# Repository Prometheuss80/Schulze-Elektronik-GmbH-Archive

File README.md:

# Schulze Elektronik GmbH Archive and Reverse Engineering Project

An independent preservation, documentation and reverse engineering project dedicated to older battery chargers, balancers and related equipment from **Schulze Elektronik GmbH**.

The purpose of this repository is to preserve technical knowledge about these devices and to make the results of ongoing reverse engineering available to the public.

Many Schulze devices are still in use today, but detailed technical information, service documentation and development tools are increasingly difficult to find.

This project attempts to document the operation of these devices and provide information and tools that can help other enthusiasts with their repair, maintenance, study and further development.

---

## Projects

### Schulze ISL8-936G

Reverse engineering of the Schulze **ISL8-936G** charger family.

Current research areas include:

* Siemens 80C537 Processor Architecture
* ROM Firmware Analysis
* External SRAM and Timekeeper M48T08
* 93LC46 EEPROM
* Firmware Execution Tracing
* Address Bus Capture and Logging
* Firmware Reconstruction
* LCD Control and Display Routines
* Keyboard and I/O Decoding
* Serial Communication
* Command Tables and Internal Firmware Structures
* Measurement System
* Factory Calibration Routines
* Service and Diagnostic Functions
* Hardware Documentation
* Development of Custom Reverse Engineering Tools

The main part of this project is the development of a complete hardware/software system capable of monitoring firmware execution and reconstructing the internal operation of the charger.

---

### Schulze ISL6-636+

Reverse Engineering and Documentation of the Schulze ISL6-636+ Charger

The research includes:

* Siemens 80C535 processor
* ROM firmware
* 93LC46 EEPROM
* HD44780 compatible LCD
* keyboard interface
* serial communication
* firmware routines
* measurement and calibration functions
* hardware documentation

ISL6 provides an interesting comparison with the later and considerably more complex ISL8 architecture.

---

### XCAL for ISL8

Research and documentation on the Schulze calibration device and automatic calibration procedures.

This research was successfully confirmed and completed. XCAL has the same function as the original Schulze device.

It is a HW switch of specified voltages for charger calibration. This BETA test module was assembled, programmed and successfully tested.

The goal was to understand the original calibration system and reproduce the functionality needed to calibrate the existing Schulze device.

---

### XTOOLS for ISL8

Research and documentation on the Schulze calibration device and automatic calibration procedures.

This XTOOLS module was the first functional SW tool for reading and writing calibrations stored in the M48T08 timekeeper in the ISL8-936G. The first research lasted three years and revealed the way to use calibration constants.

It was manufactured and successfully tested, operating on the principle of a ROM adapter, with an IO switch ROM with XTOOLS and a ROM with FW850EN.

The goal was to understand the original calibration system and reproduce the functionality needed to calibrate the existing Schulze device.

The original standalone XTOOLS remains part of the archive. A later, integrated XTOOLS implementation has also been developed for the ISL8 firmware, including calibration editing and Timekeeper service functions.

---

### ISL6 XTOOLS and GUI

Completed XTOOLS and GUI development projects for the ISL6 family will be documented separately in this archive. Their project pages will describe supported models, implementation details and hardware testing.

---

### LipoProfiBal06

Hardware analysis of the Schulze LipoProfiBal08 and LipoProfiBal14 battery balancer.

This project includes:

* reverse engineering of the original hardware
* measurement system analysis
* power stage balancing
* MOSFET control
* isolated gate control circuits
* current measurement
* power supply architecture
* communication interface
* development of a modern replacement printed circuit board (PCB)

The new printed circuit board is to maintain the principles of operation of the original device while using components that are available today.

---

## Factory Calibration Research

Some Schulze charger firmware contains factory calibration and diagnostic functions that are typically inaccessible to the user.

Part of this project is to investigate these routines and document their operation. A number of ISL8 chargers have been successfully exposed and run as factory calibration.

Where firmware modifications are required, the preferred approach of this repository is to provide **patches and patching tools, rather than redistributing complete copyrighted firmware images**.

The user should obtain the original firmware from their own device and apply the documented modification locally.

A hardware-tested **Factory Calibration F2 Patcher** is available for ISL8 firmware versions **8.10 DE, 8.10 EN, 8.50 DE and 8.50 EN**. It enables access to the existing factory calibration procedure through F2, changes the displayed firmware identification, and updates the modification date and time. The patching tool verifies the SHA-256 of the user-supplied original firmware and does not redistribute Schulze firmware images.

---

## Author

**Martin Stránský (Prometheuss80)**

Independent research, firmware reverse engineering, development, hardware analysis and testing.

Copyright © 2026 Martin Stránský (Prometheuss80).

GitHub: [Prometheuss80](https://github.com/Prometheuss80)

---

## Licensing

Original tools and code authored for this archive may be released under the **MIT License**; see the `LICENSE` file or the license stated within each project directory for the exact scope.

The MIT License does **not** apply to original Schulze Elektronik firmware or third-party materials unless their respective rights holders authorize it. Individual project directories may have their own licensing terms.

---

## Repository Philosophy

This repository is primarily intended as a **technical archive and resource for collaborative research**.

The project is being developed in my spare time and it is not possible for me to work on all areas at the same time.

Anyone interested in a specific part of the project is welcome to study the available materials, create a fork and continue the research independently.

Useful discoveries, fixes, documentation and improvements are welcome.

It is not necessary to understand the entire system. Individual areas such as firmware analysis, 8051 assembly, analog electronics, PCB design, calibration, communication protocols or software tools can be explored independently.

---

## Contributions

Contributions are welcome.

You can:

* fork the repository
* explore any piece of hardware or firmware
* improve the documentation
* develop analytical tools
* verify existing knowledge
* submit fixes
* open an Issue with additional information
* submit a Pull Request with improvements

Since this is a project focused on preservation and leisure research, responses to Issues and Pull Requests may not always be immediate.

---

## Original material from Schulze

This repository distinguishes between:

1. original work created within the scope of this reverse engineering project and

2. copyrighted material originally created by Schulze Elektronik GmbH.

Reverse engineering notes, original software tools, measurements, photos, diagrams, and newly created documentation may be published here.

Original firmware images, manuals, and other copyrighted material from Schulze will only be included where it is known that redistribution rights allow it.

If redistribution rights are not clear, the repository will instead document the material and provide information needed for users who already own the original files or hardware.

---

## Security

Battery chargers and balancers can operate with significant electrical power.

Modified firmware, calibration procedures, and experimental hardware can disable or bypass normal protection mechanisms.

Improper calibration or modification can lead to inaccurate voltage or current measurements, battery damage, equipment damage, fire, or other hazardous conditions.

The information in this repository is provided for research, repair, and educational purposes. Anyone reproducing experiments or modifications is responsible for verifying the results and using appropriate safety precautions.

---

## Project Status

**Work in progress.**

A significant amount of reverse engineering has already been completed, particularly for the ISL8 platform. The standalone ISL8 XTOOLS, integrated ISL8 XTOOLS, ISL6 XTOOLS and ISL6 GUI projects have reached working, hardware-tested milestones. Other investigations and documentation remain ongoing.

This independent archive is maintained by Martin Stránský (Prometheuss80).

It is not affiliated with, sponsored by, or endorsed by Schulze Elektronik.

All trademarks and original product names remain the property of their respective owners.

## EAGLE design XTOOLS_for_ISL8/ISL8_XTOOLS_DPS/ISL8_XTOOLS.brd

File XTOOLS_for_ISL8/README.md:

# XTOOLS for Schulze ISL8

**XTOOLS** is an independent service and maintenance tool developed for the **Schulze ISL8 battery charger**.

It was the first project created during the ISL8 reverse-engineering work and originally started as a tool for accessing and managing the charger voltage calibration data.

Unlike a PC-based diagnostic utility, **XTOOLS runs directly on the original ISL8 hardware**.

It contains its own initialization routines and does not require the original Schulze firmware to operate.

---

## Overview

After startup, XTOOLS performs the initialization required to take control of the ISL8 hardware.

This includes:

* initialization of the main CPU
* initialization and configuration of the LCD
* initialization of required peripherals
* configuration of the charger hardware
* placing the charger power circuitry into a safe idle state
* initialization of the memory interfaces

After the hardware initialization is complete, the XTOOLS service environment is started.

The program then provides direct access to selected service and maintenance functions of the charger.

---

## Calibration Data

XTOOLS was originally developed to investigate and service the ISL8 voltage calibration system.

The tool can:

* read the existing calibration values
* display calibration information
* access calibration data stored in the Timekeeper memory
* write calibration values back to the Timekeeper

This made it possible to investigate the calibration system independently of the original charger firmware.

---

## Timekeeper Service

The ISL8 uses a Timekeeper memory for persistent configuration and operating data.

XTOOLS provides service functions for this memory, including:

* reading stored data
* writing selected data
* clearing the Timekeeper contents
* preparing a replacement Timekeeper for installation

This is particularly useful when the original Timekeeper has failed or must be replaced.

### New Timekeeper Initialization

XTOOLS provides a procedure for correctly preparing a new Timekeeper for use in an ISL8 charger.

During this process, the tool restores information required by the charger and reconstructs the charger serial number using data stored separately in an EEPROM on the ISL8 main board.

This makes XTOOLS an important service tool when replacing a failed Timekeeper device.

---

## User Data Service

XTOOLS also provides maintenance functions for selected user configuration data.

Available functions include:

* user password reset
* user name reset
* clearing selected persistent user data

These functions can be useful when servicing a charger for which the original user configuration is no longer known.

---

## Standalone Operation

One of the important characteristics of XTOOLS is that it is a **standalone firmware environment**.

The original Schulze ISL8 firmware is not required for XTOOLS operation.

XTOOLS performs its own:

1. CPU initialization
2. LCD initialization
3. hardware initialization
4. safe-state configuration
5. memory initialization
6. service application startup

The ISL8 therefore effectively operates as dedicated XTOOLS service hardware while the tool is active.

---

## XTOOLS Hardware Adapter

The project includes a dedicated hardware adapter that allows the ISL8 to switch between the original charger ROM and the XTOOLS ROM.

The adapter makes it possible to retain normal operation of the charger while providing access to the independent XTOOLS service environment when required.

The switching system is controlled by a **PIC microcontroller**.

---

## Repository Contents

This directory contains the complete XTOOLS project, including:

### XTOOLS Firmware

The complete source project for the XTOOLS firmware.

The firmware was developed using the **Keil development environment**.

### XTOOLS Adapter

Complete hardware project for the XTOOLS adapter used with the ISL8 charger.

### PCB Manufacturing Data

Manufacturing files for the XTOOLS adapter PCB, including Gerber data required for PCB production.

### PIC Switch Controller

Source/project files for the PIC microcontroller responsible for switching between:

* the original ISL8 ROM
* the XTOOLS ROM

This allows the charger to operate normally with its original firmware or boot into XTOOLS for servicing.

---

## Project Purpose

XTOOLS was created primarily as a **repair, calibration, preservation and reverse-engineering tool** for existing Schulze ISL8 chargers.

The project demonstrates that the ISL8 hardware can be initialized and operated independently of the original firmware and provides direct access to service functions that are useful when maintaining aging hardware.

In particular, XTOOLS can assist with:

* calibration data investigation
* calibration data backup and restoration
* Timekeeper replacement
* Timekeeper initialization
* recovery of charger identification data
* password recovery/reset
* user configuration reset
* hardware research and reverse engineering

---

## Important: Back Up Original Data

Before modifying or clearing the Timekeeper, always create a backup of the original contents whenever possible.

Some data stored in the charger may be unique to the individual device.

Do not erase or overwrite the original memory until a verified backup has been created.

---

## Safety Warning

XTOOLS operates directly on the hardware of a battery charger.

While XTOOLS initializes the charger hardware into an idle state before entering the service application, modifications to calibration data or persistent memory can affect subsequent charger operation.

Incorrect calibration data can cause incorrect voltage measurement and may result in unsafe battery charging.

After modifying calibration or replacing persistent memory, the charger should be fully verified and calibrated before being returned to normal operation.

Use this project only if you understand the hardware and the consequences of modifying its persistent configuration.

---

## Development Status

XTOOLS is a functional project developed from reverse engineering of the Schulze ISL8 hardware.

Additional documentation will be added as the historical development files, hardware documentation and source code are organized for public release.

---

## Disclaimer

XTOOLS is an independent project.

It is not an official Schulze Elektronik product and is not affiliated with, sponsored by, or endorsed by Schulze Elektronik.

Schulze product names are used only to identify the hardware for which this service tool was developed.

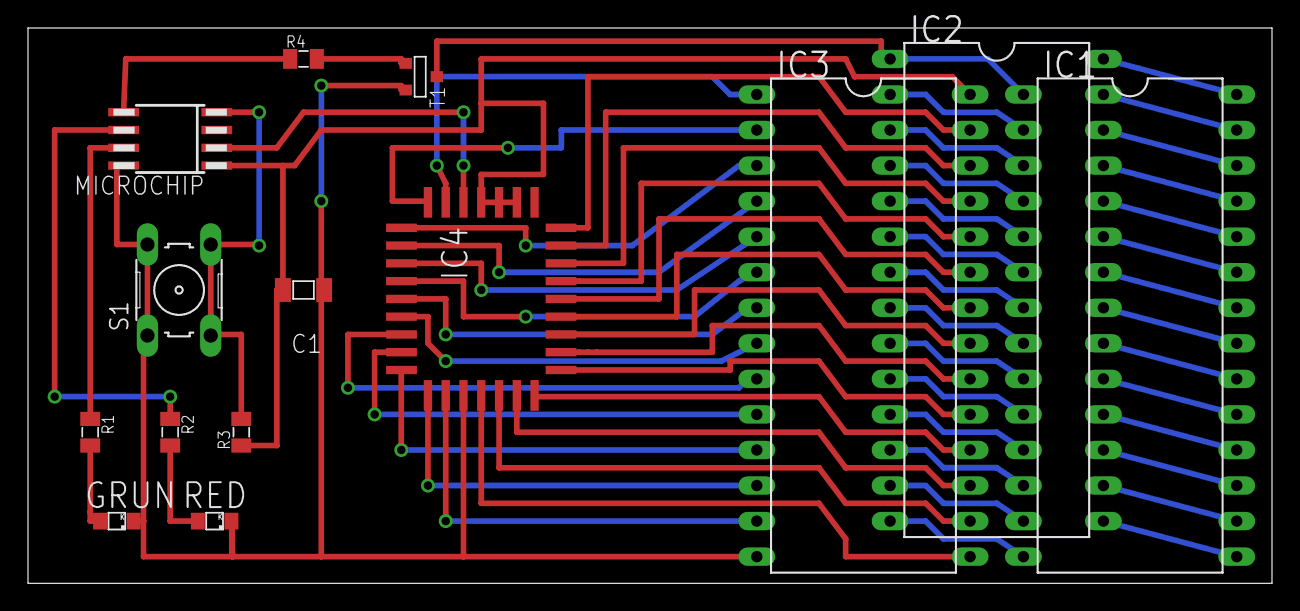
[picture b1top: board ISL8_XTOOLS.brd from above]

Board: 2 copper layers, 88.9 x 39.7 mm, 14 parts (0 on the bottom side), 64 nets.

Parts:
C1: 100nF; 1206
GRUN: ISL_8; HSMC670
IC1: DIP28_ISL8_TMKPR; DIL28-6
IC2: DIP28_XTOOLS_TMKPR; DIL28-6
IC3: DIP28_ISL8_EPROM; DIL28-6
IC4: W27C010; PLCC32R
MICROCHIP: PIC12C509SM; SO-08M
R1, R2, R4: 1k; 0805
R3: 10k; 0805
RED: XTOOLS; HSMC670
S1: SWITCH; B3F-10XX
T1: RESET; SOT-23

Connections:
0V: C1.1, GRUN.K, IC3.14, IC4.16, MICROCHIP.8, RED.K, S1.1, S1.2, T1.2
+5V: C1.2, IC3.28, IC4.1, IC4.31, IC4.32, MICROCHIP.1, R3.1
A0: IC3.10, IC4.12
A1: IC3.9, IC4.11
A2: IC3.8, IC4.10
A3: IC3.7, IC4.9
A4: IC3.6, IC4.8
A5: IC3.5, IC4.7
A6: IC3.4, IC4.6
A7: IC3.3, IC4.5
A8: IC3.25, IC4.27
A9: IC3.24, IC4.26
A10: IC3.21, IC4.23
A11: IC3.23, IC4.25
A12: IC3.2, IC4.4
A13: IC3.26, IC4.28
A14: IC3.27, IC4.29
A15: IC3.1, IC4.3
A16: IC4.2, MICROCHIP.2
CE: IC3.20, IC4.22
D0: IC3.11, IC4.13
D1: IC3.12, IC4.14
D2: IC3.13, IC4.15
D3: IC3.15, IC4.17
D4: IC3.16, IC4.18
D5: IC3.17, IC4.19
D6: IC3.18, IC4.20
D7: IC3.19, IC4.21
unnamed: IC1.1, IC2.1, T1.3
unnamed: MICROCHIP.7, R1.1
unnamed: MICROCHIP.6, R2.1
unnamed: R2.2, RED.A
unnamed: GRUN.A, R1.2
unnamed: MICROCHIP.5, R4.1
unnamed: MICROCHIP.4, R3.2, S1.3, S1.4
unnamed: IC1.2, IC2.2
unnamed: IC1.3, IC2.3
unnamed: IC1.4, IC2.4
unnamed: IC1.5, IC2.5
unnamed: R4.2, T1.1
unnamed: IC1.6, IC2.6
unnamed: IC1.7, IC2.7
unnamed: IC1.8, IC2.8
unnamed: IC1.9, IC2.9
unnamed: IC1.10, IC2.10
unnamed: IC1.11, IC2.11
unnamed: IC1.12, IC2.12
unnamed: IC1.13, IC2.13
unnamed: IC1.14, IC2.14
unnamed: IC1.15, IC2.15
unnamed: IC1.16, IC2.16
unnamed: IC1.17, IC2.17
unnamed: IC1.18, IC2.18
unnamed: IC1.19, IC2.19
unnamed: IC1.20, IC2.20
unnamed: IC1.21, IC2.21
unnamed: IC1.22, IC2.22
unnamed: IC1.23, IC2.23
unnamed: IC1.24, IC2.24
unnamed: IC1.25, IC2.25
unnamed: IC1.26, IC2.26
unnamed: IC1.27, IC2.27
unnamed: IC1.28, IC2.28
OE: IC3.22, IC4.24

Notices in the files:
parts and their libraries:
Copyright (C) PaJa 2001-2011
